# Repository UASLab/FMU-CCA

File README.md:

# FMU-CCA
Circuit Card Assembly for FMU

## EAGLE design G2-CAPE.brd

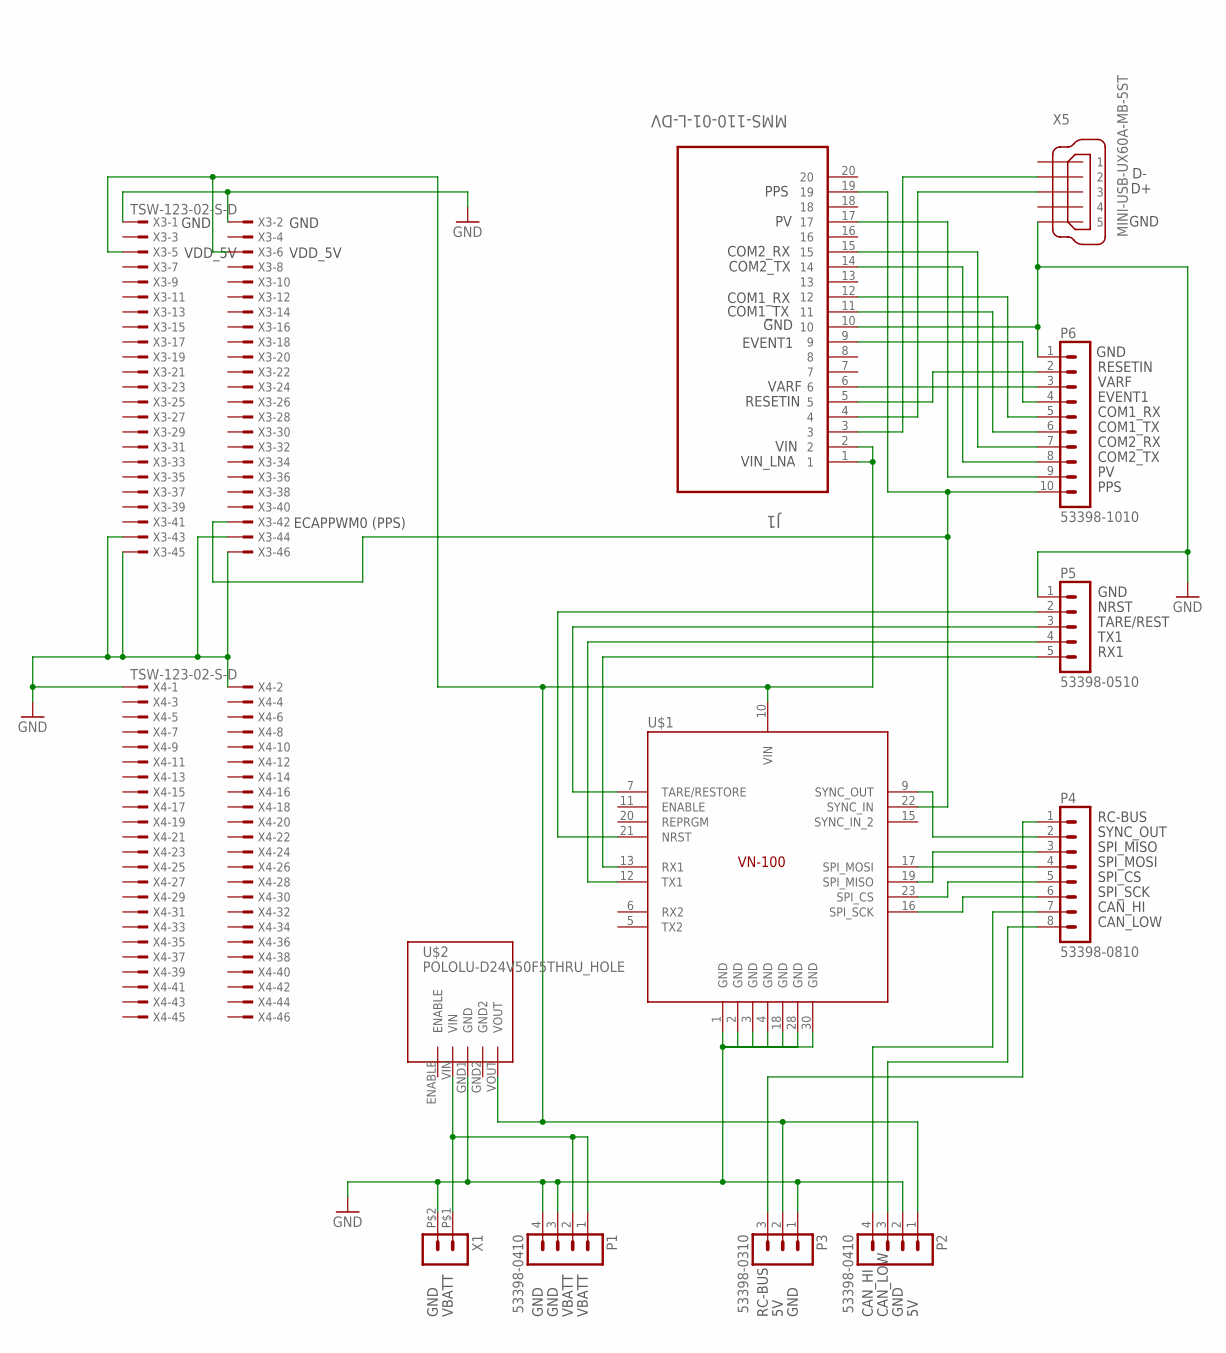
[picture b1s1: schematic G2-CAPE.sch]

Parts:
J1: MMS-110-01-L-DV; SAMTEC_MMS-110-01-L-DV
P1, P2: 53398-0410
P3: 53398-0310
P4: 53398-0810
P5: 53398-0510
P6: 53398-1010
U$1: VN100NORMAL; 7X8CASTLE
U$2: POLOLU-D24V50F5THRU_HOLE; POLOLU-D24V50F5
X1: HEADER_POS2_; 43650-0203
X3, X4: TSW-123-02-S-D
X5: MINI-USB-UX60A-MB-5ST; UX60A-MB-5ST

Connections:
GND: J1.10, P1.3, P1.4, P2.2, P3.1, P5.1, P6.1, U$1.1 (GND), U$1.2 (GND), U$1.3 (GND), U$1.4 (GND), U$1.18 (GND), U$1.28 (GND), U$1.30 (GND), U$2.GND1 (GND), X1.P$2 (2), X3.1, X3.2, X3.43, X3.44, X3.45, X3.46, X4.1, X4.2, X5.5
unnamed: P1.1, P1.2, U$2.VIN, X1.P$1 (1)
unnamed: J1.19, P6.10, U$1.22 (SYNC_IN), X3.42
unnamed: J1.1, J1.2, P2.1, P3.2, U$1.10 (VIN), U$2.VOUT, X3.5, X3.6
unnamed: P5.5, U$1.13 (RX1)
unnamed: P3.3, P4.1
unnamed: P2.3, P4.8
unnamed: P2.4, P4.7
unnamed: P5.4, U$1.12 (TX1)
unnamed: P4.2, U$1.9 (SYNC_OUT)
unnamed: P4.3, U$1.19 (SPI_MISO)
unnamed: P5.3, U$1.7 (TARE/RESTORE)
unnamed: P5.2, U$1.21 (NRST)
unnamed: J1.3, X5.2
unnamed: P4.4, U$1.17 (SPI_MOSI)
unnamed: P4.5, U$1.23 (SPI_CS)
unnamed: P4.6, U$1.16 (SPI_SCK)
unnamed: J1.4, X5.3
unnamed: J1.5, P6.2
unnamed: J1.6, P6.3
unnamed: J1.9, P6.4
unnamed: J1.12, P6.5
unnamed: J1.11, P6.6
unnamed: J1.15, P6.7
unnamed: J1.14, P6.8
unnamed: J1.17, P6.9

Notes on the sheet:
ECAPPWM0 (PPS)
PPS
VIN
VIN_LNA
GND
VDD_5V
RESETIN
VARF
EVENT1
COM1_RX
COM1_TX
COM2_TX
COM2_RX
NRST
TARE/REST
TX1
RX1
SYNC_OUT
SPI_MISO
SPI_MOSI
SPI_CS
SPI_SCK
CAN_HI
CAN_LOW
RC-BUS
VBATT

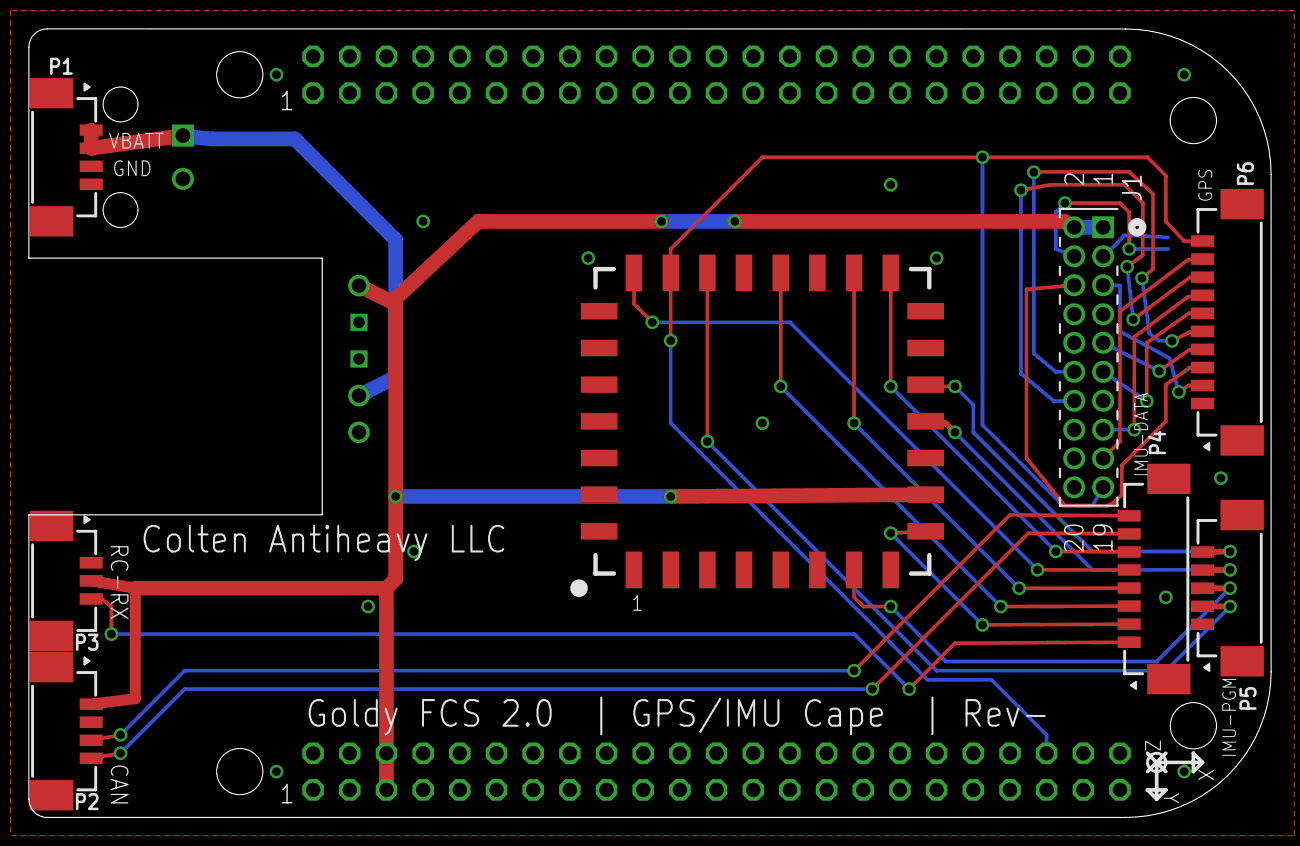
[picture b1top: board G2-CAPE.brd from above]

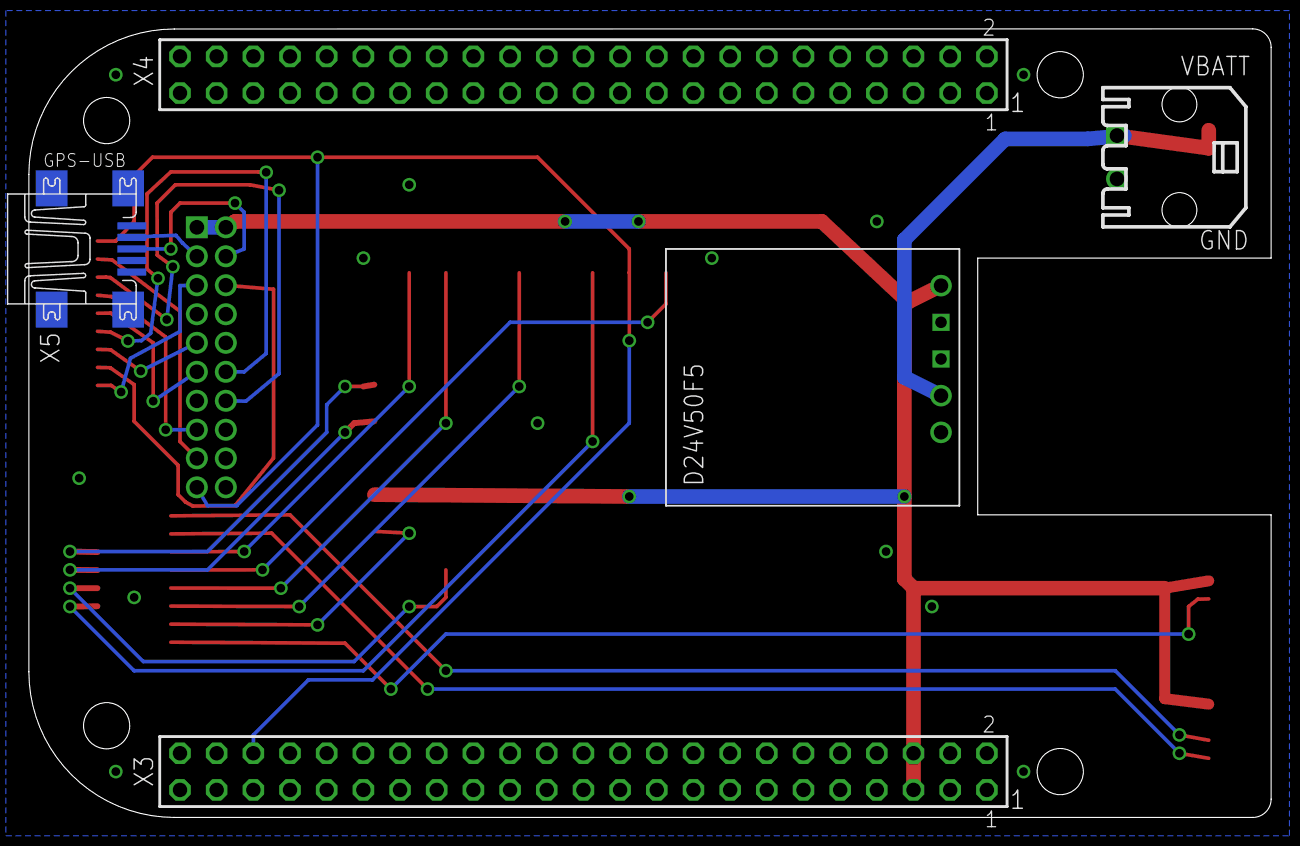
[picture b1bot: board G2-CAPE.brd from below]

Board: 2 copper layers, 86.0 x 54.6 mm, 13 parts (5 on the bottom side), 26 nets.

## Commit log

2015-12-07 Initial revision.

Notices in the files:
parts and their libraries:
con-molex-picoblade: Copyright (C) 2010, Bob Starr
